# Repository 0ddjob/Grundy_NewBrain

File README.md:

# Grundy_NewBrain
Hopefully I can contribute something to the community.<br>

My current goal is to re-design the "store board" to use a 32KB SRAM instead of the two banks of 16KB DRAM.<br>

I think this is the last remaining fault in my machine.<br>

Failing ... or succeeding ... that, I'd like to try at a 64KB external SRAM board.<br>

{Fri 15-Sept-2023}<br>
Sent SRAM Store Board prototype for fabrication<br>
{Sat 1-Mar-2025}<br>
Well, what a disaster that was.  Fixed my (obvious) mistakes and have sent the updated design for fabrication.<br>

My YouTube video playlist - note, most are my very early videos so probably a bit rough:<br>
[https://www.youtube.com/playlist?list=PL5pwokf56wMKPswNvQZJsGPXETtgRD57M](https://www.youtube.com/playlist?list=PL5pwokf56wMKPswNvQZJsGPXETtgRD57M)

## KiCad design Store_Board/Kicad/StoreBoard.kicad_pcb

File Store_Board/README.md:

# Grundy NewBrain Store Board

This is the internal RAM board in the NewBrain.<br>

It comprises two banks of 16KB, making 32KB in total.  Each bank has eight MM5290N-2 (16K x 1bit) DRAM chips.<br>

The DRAM is multiplexed using two RAS signals (RAS16 for bank 1 and RAS32 for bank 2) and one CAS signal.<br>

My idea to replace these DRAM with a single 32KB SRAM is as follows:<br>
- There are only eight address lines taken across to the store board: A0 to A6 & A14<br>
- As per other DRAM-to-SRAM designs, latch the RAS signals and apply with CAS<br>
- Simplify the two RAS16 & RAS32 signals to a single RAS signal for clocking the row address latch<br>

Let's see ... (4-Sep-2023)<br>

Thanks to John Bradley for his Kicad schematics:<br>
https://github.com/flypie/NewBrain<br>

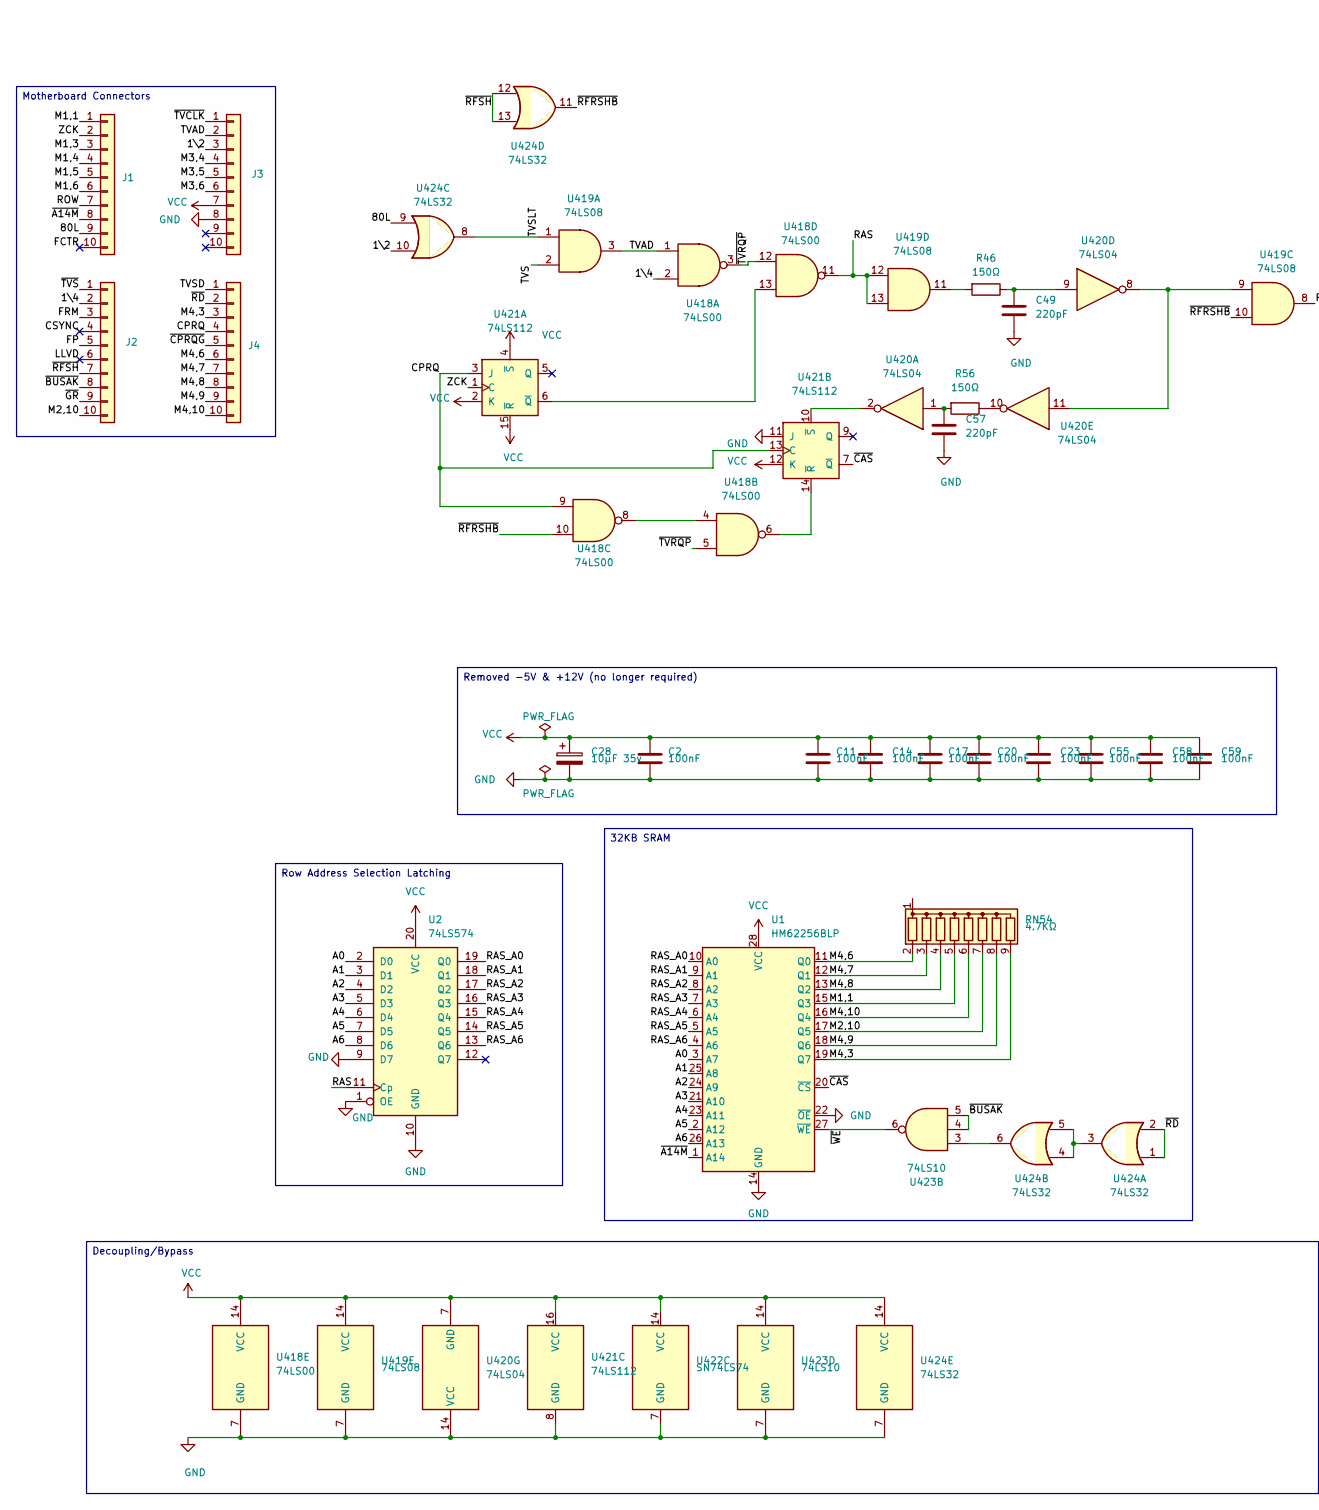
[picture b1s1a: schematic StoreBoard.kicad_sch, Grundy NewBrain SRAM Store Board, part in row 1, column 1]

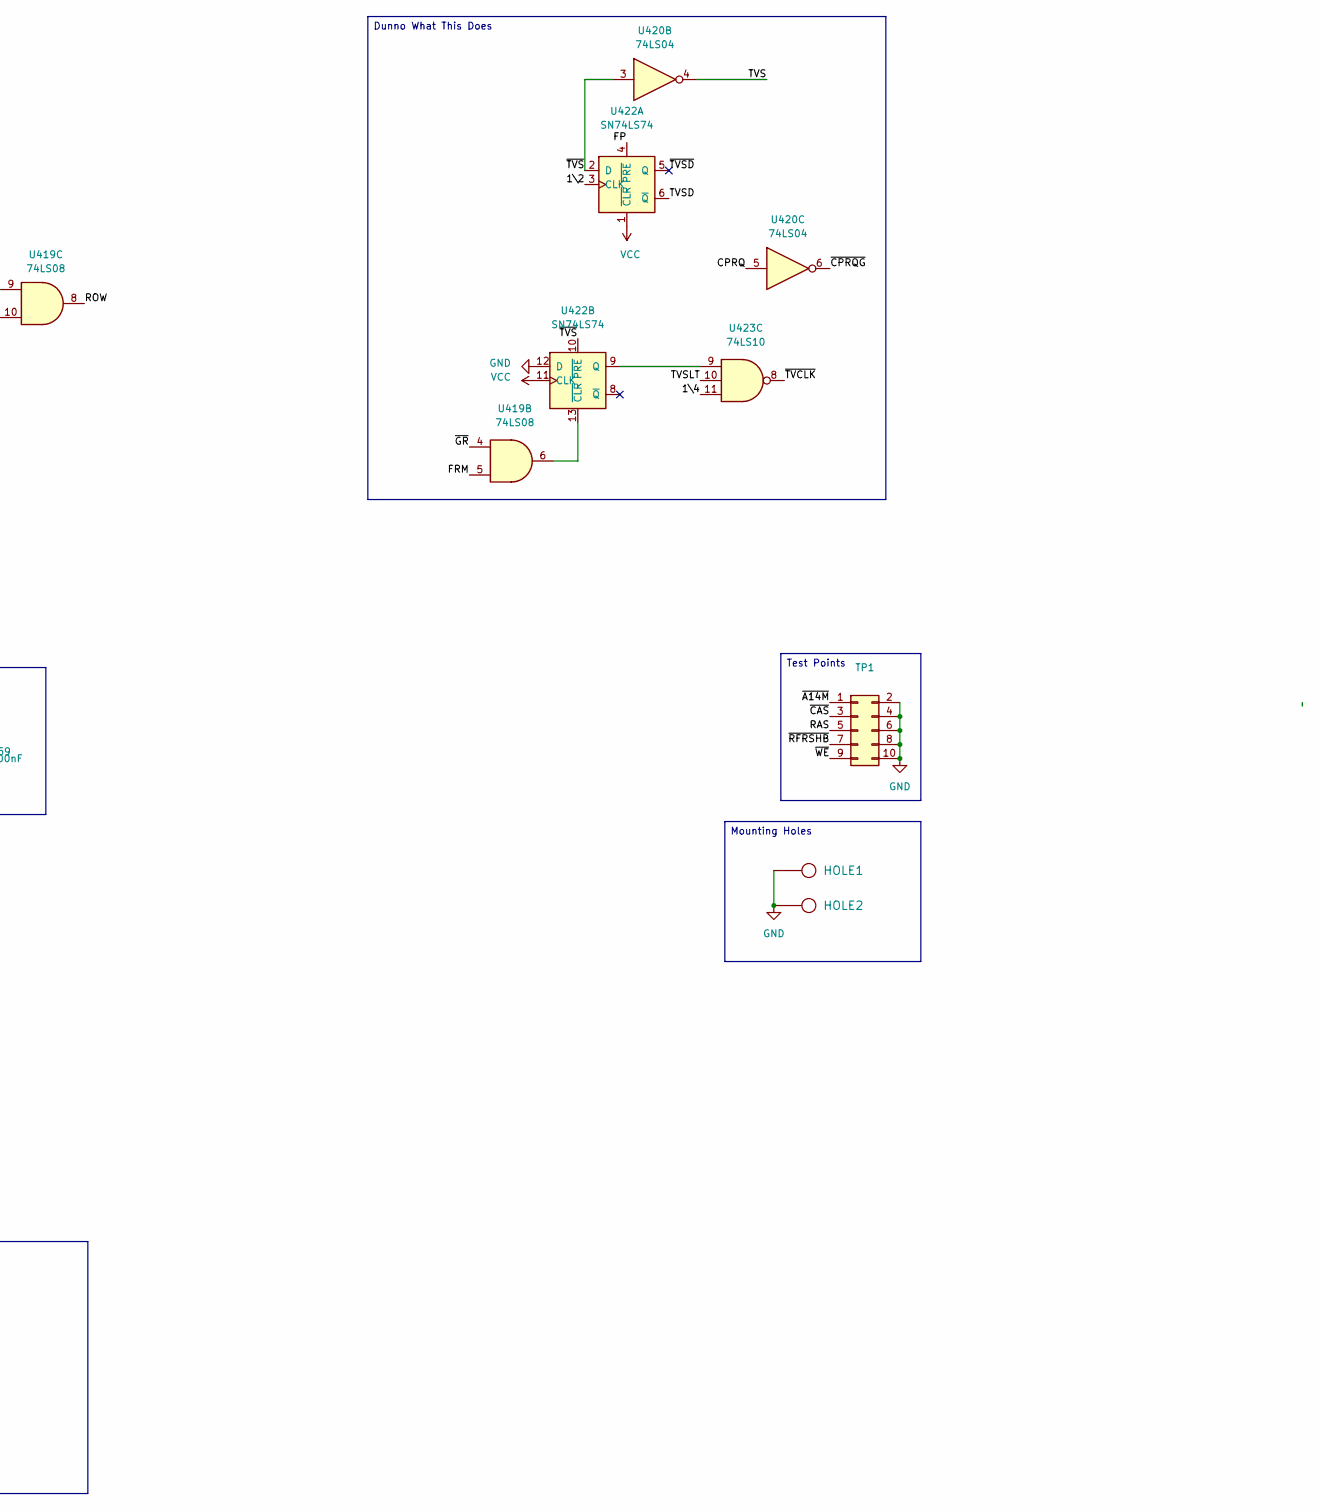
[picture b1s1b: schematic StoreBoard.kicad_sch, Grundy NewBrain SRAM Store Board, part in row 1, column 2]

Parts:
C2, C11, C14, C17, C20, C23, C55, C58, C59: 100nF; C_Disc_D3.0mm_W1.6mm_P2.50mm
C28: 10µF 35v; CP_Radial_D5.0mm_P2.00mm
C49, C57: 220pF; C_Disc_D3.0mm_W1.6mm_P2.50mm
HOLE1, HOLE2: HOLE; MountingHole_3.2mm_M3_Pad
J1, J2, J3, J4: Conn_01x10; PinHeader_1x10_P2.54mm_Vertical
R46, R56: 150Ω; R_Axial_DIN0207_L6.3mm_D2.5mm_P10.16mm_Horizontal
RN54: 4.7KΩ; R_Array_SIP9
TP1: Conn_02x05_Odd_Even; PinHeader_2x05_P2.54mm_Vertical
U1: HM62256BLP; DIP-28_W15.24mm
U2: 74LS574; DIP-20_W7.62mm
U418: 74LS00; DIP-14_W7.62mm
U419: 74LS08; DIP-14_W7.62mm
U420: 74LS04; DIP-14_W7.62mm
U421: 74LS112; DIP-16_W7.62mm
U422: SN74LS74; DIP-14_W7.62mm
U423: 74LS10; DIP-14_W7.62mm
U424: 74LS32; DIP-14_W7.62mm

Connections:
/1\2: J3.3, U422.3 (CLK), U424.10
/1\4: J2.2, U418.2, U423.11
/80L: J1.9, U424.9
/A0: U1.3 (A7), U2.2 (D0)
/A1: U1.25 (A8), U2.3 (D1)
/A2: U1.24 (A9), U2.4 (D2)
/A3: U1.21 (A10), U2.5 (D3)
/A4: U1.23 (A11), U2.6 (D4)
/A5: U1.2 (A12), U2.7 (D5)
/A6: U1.26 (A13), U2.8 (D6)
/CPRQ: J4.4, U418.9, U420.5, U421.3 (J), U421.13 (C)
/CSYNC: J2.4
/FCTR: J1.10
/FP: J2.5, U422.4 (~PRE)
/FRM: J2.3, U419.5
/LLVD: J2.6
/M1,1: J1.1, RN54.5 (R4), U1.15 (Q3)
/M1,3: J1.3
/M1,4: J1.4
/M1,5: J1.5
/M1,6: J1.6
/M2,10: J2.10, RN54.7 (R6), U1.17 (Q5)
/M3,4: J3.4
/M3,5: J3.5
/M3,6: J3.6
/M4,3: J4.3, RN54.9 (R8), U1.19 (Q7)
/M4,6: J4.6, RN54.2 (R1), U1.11 (Q0)
/M4,7: J4.7, RN54.3 (R2), U1.12 (Q1)
/M4,8: J4.8, RN54.4 (R3), U1.13 (Q2)
/M4,9: J4.9, RN54.8 (R7), U1.18 (Q6)
/M4,10: J4.10, RN54.6 (R5), U1.16 (Q4)
/RAS: TP1.5, U2.11 (Cp), U418.11, U419.12, U419.13
/RAS_A0: U1.10 (A0), U2.19 (Q0)
/RAS_A1: U1.9 (A1), U2.18 (Q1)
/RAS_A2: U1.8 (A2), U2.17 (Q2)
/RAS_A3: U1.7 (A3), U2.16 (Q3)
/RAS_A4: U1.6 (A4), U2.15 (Q4)
/RAS_A5: U1.5 (A5), U2.14 (Q5)
/RAS_A6: U1.4 (A6), U2.13 (Q6)
/ROW: J1.7, U419.8
/TVAD: J3.2, U418.1, U419.3
/TVS: U419.2, U420.4
/TVSD: J4.1, U422.6 (~Q)
/TVSLT: U419.1, U423.10, U424.8
/ZCK: J1.2, U421.1 (C)
/~A14M: J1.8, TP1.1, U1.1 (A14)
/~BUSAK: J2.8, U423.4, U423.5
/~CAS: TP1.3, U1.20 (~CS), U421.7 (~Q)
/~CPRQG: J4.5, U420.6
/~GR: J2.9, U419.4
/~RD: J4.2, U424.1, U424.2
/~RFRSHB: TP1.7, U418.10, U419.10, U424.11
/~RFSH: J2.7, U424.12, U424.13
/~TVCLK: J3.1, U423.8
/~TVRQP: U418.3, U418.5, U418.12
/~TVSD: U422.5 (Q)
/~TVS: J2.1, U420.3, U422.2 (D), U422.10 (~PRE)
/~WE: TP1.9, U1.27 (~WE), U423.6
GND: C2.2, C11.2, C14.2, C17.2, C20.2, C23.2, C28.2, C49.2, C55.2, C57.2, C58.2, C59.2, HOLE1.1, HOLE2.1, J3.8, TP1.2, TP1.4, TP1.6, TP1.8, TP1.10, U1.14 (GND), U1.22 (~OE), U2.1 (OE), U2.9 (D7), U2.10 (GND), U418.7 (GND), U419.7 (GND), U420.14 (VCC), U421.8 (GND), U421.11 (J), U422.7 (GND), U422.12 (D), U423.7 (GND), U424.7 (GND)
unnamed: C49.1, R46.1, U420.9
unnamed: C57.1, R56.2, U420.1
unnamed: R46.2, U419.11
unnamed: R56.1, U420.10
unnamed: U418.4, U418.8
unnamed: U419.9, U420.8, U420.11
unnamed: U418.13, U421.6 (~Q)
unnamed: U418.6, U421.14 (~R)
unnamed: U420.2, U421.10 (~S)
unnamed: U422.9 (Q), U423.9
unnamed: U419.6, U422.13 (~CLR)
unnamed: U423.3, U424.6
unnamed: U424.3, U424.4, U424.5
VCC: C2.1, C11.1, C14.1, C17.1, C20.1, C23.1, C28.1, C55.1, C58.1, C59.1, J3.7, U1.28 (VCC), U2.20 (VCC), U418.14 (VCC), U419.14 (VCC), U420.7 (GND), U421.2 (K), U421.4 (~S), U421.12 (K), U421.15 (~R), U421.16 (VCC), U422.1 (~CLR), U422.11 (CLK), U422.14 (VCC), U423.14 (VCC), U424.14 (VCC)

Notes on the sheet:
32KB SRAM
Decoupling/Bypass
Row Address Selection Latching
Test Points
Mounting Holes
Motherboard Connectors
Removed -5V & +12V (no longer required)
Dunno What This Does

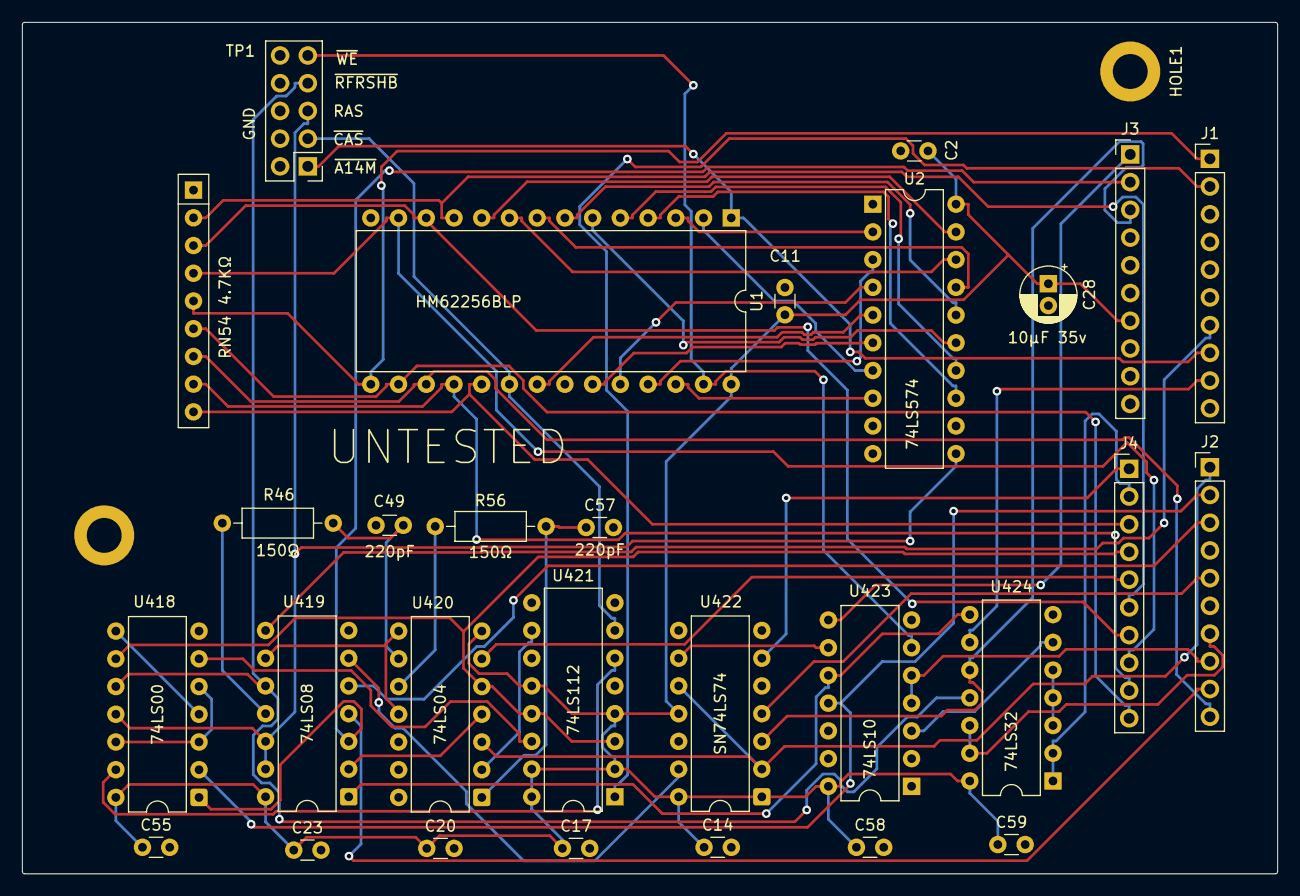
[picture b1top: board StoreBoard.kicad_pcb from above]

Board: 2 copper layers, 115.0 x 78.0 mm, 31 parts (0 on the bottom side), 62 nets.

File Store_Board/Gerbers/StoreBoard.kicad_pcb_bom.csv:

Designator,Quantity,Value,Footprint,Package,MPN,DNP,Mount_Type
"C11, C14, C17, C2, C20, C23, C55, C58, C59",9,100nF,C_Disc_D3.0mm_W1.6mm_P2.50mm,,,,tht
C28,1,10µF 35v,CP_Radial_D5.0mm_P2.00mm,,,,tht
"C49, C57",2,220pF,C_Disc_D3.0mm_W1.6mm_P2.50mm,,,,tht
"HOLE1, HOLE2",2,HOLE,MountingHole_3.2mm_M3_Pad,,,,tht
"J1, J2, J3, J4",4,Conn_01x10,PinHeader_1x10_P2.54mm_Vertical,,,,tht
"R46, R56",2,150Ω,R_Axial_DIN0207_L6.3mm_D2.5mm_P10.16mm_Horizontal,,,,tht
RN54,1,4.7KΩ,R_Array_SIP9,,,,tht
TP1,1,Conn_02x05_Odd_Even,PinHeader_2x05_P2.54mm_Vertical,,,,tht
U1,1,HM62256BLP,DIP-28_W15.24mm,,,,tht
U2,1,74LS574,DIP-20_W7.62mm,,,,tht
U418,1,74LS00,DIP-14_W7.62mm,,,,tht
U419,1,74LS08,DIP-14_W7.62mm,,,,tht
U420,1,74LS04,DIP-14_W7.62mm,,,,tht
U421,1,74LS112,DIP-16_W7.62mm,,,,tht
U422,1,SN74LS74,DIP-14_W7.62mm,,,,tht
U423,1,74LS10,DIP-14_W7.62mm,,,,tht
U424,1,74LS32,DIP-14_W7.62mm,,,,tht

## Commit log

2023-08-30 Expansion connector pinout
2023-08-31 Initial 32KB SRAM Design
2023-08-31 Corrections to original schematic
2023-08-31 PCB layout of (untested) SRAM Store Board
2023-08-31 PCB for testing
2023-08-31 Refinements
2023-08-31 PCB refinements
2023-08-31 Ready for testing, I think
2023-08-31 Original DRAM schematic
2023-08-31 Updated SRAM schematic (work in progress)
2023-09-01 Added testpoints
2023-09-02 Further refinements
2023-09-04 Further refinements to RAS handling
2023-09-04 Noting the redrawn schematic has errors
2023-09-14 Final update before test fabrication
2023-09-15 Sent SRAM store board prototype for fabrication
2025-03-01 Corrected footprints
2025-03-01 Updated Store Board 3D image
